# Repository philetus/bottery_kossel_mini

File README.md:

bottery kossel mini
===================

emerald bottery customizations for kossel mini reprap

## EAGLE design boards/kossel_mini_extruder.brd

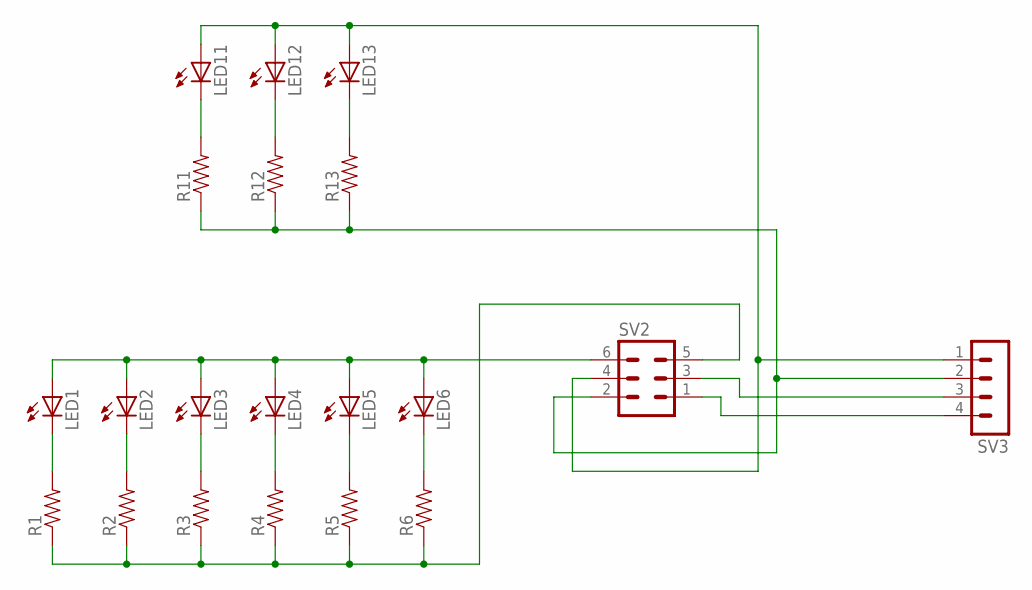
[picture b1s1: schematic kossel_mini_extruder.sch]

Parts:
LED1, LED2, LED3, LED4, LED5, LED6, LED11, LED12, LED13: LED0805; CHIPLED_0805
R1, R2, R3, R4, R5, R6, R11, R12, R13: RESISTOR0805-RES; 0805
SV2: MA03-2
SV3: MA04-1

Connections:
GND: R1.1, R2.1, R3.1, R4.1, R5.1, R6.1, SV2.5
HOT_12V: R11.1, R12.1, R13.1, SV2.2, SV3.2
HOT_SIG: LED11.A, LED12.A, LED13.A, SV2.4, SV3.1
unnamed: LED1.C, R1.2
unnamed: LED2.C, R2.2
unnamed: LED3.C, R3.2
unnamed: LED4.C, R4.2
unnamed: LED5.C, R5.2
unnamed: LED6.C, R6.2
unnamed: LED11.C, R11.2
unnamed: LED12.C, R12.2
unnamed: LED13.C, R13.2
THERM_GND: SV2.1, SV3.4
THERM_SIG: SV2.3, SV3.3
VCC: LED1.A, LED2.A, LED3.A, LED4.A, LED5.A, LED6.A, SV2.6

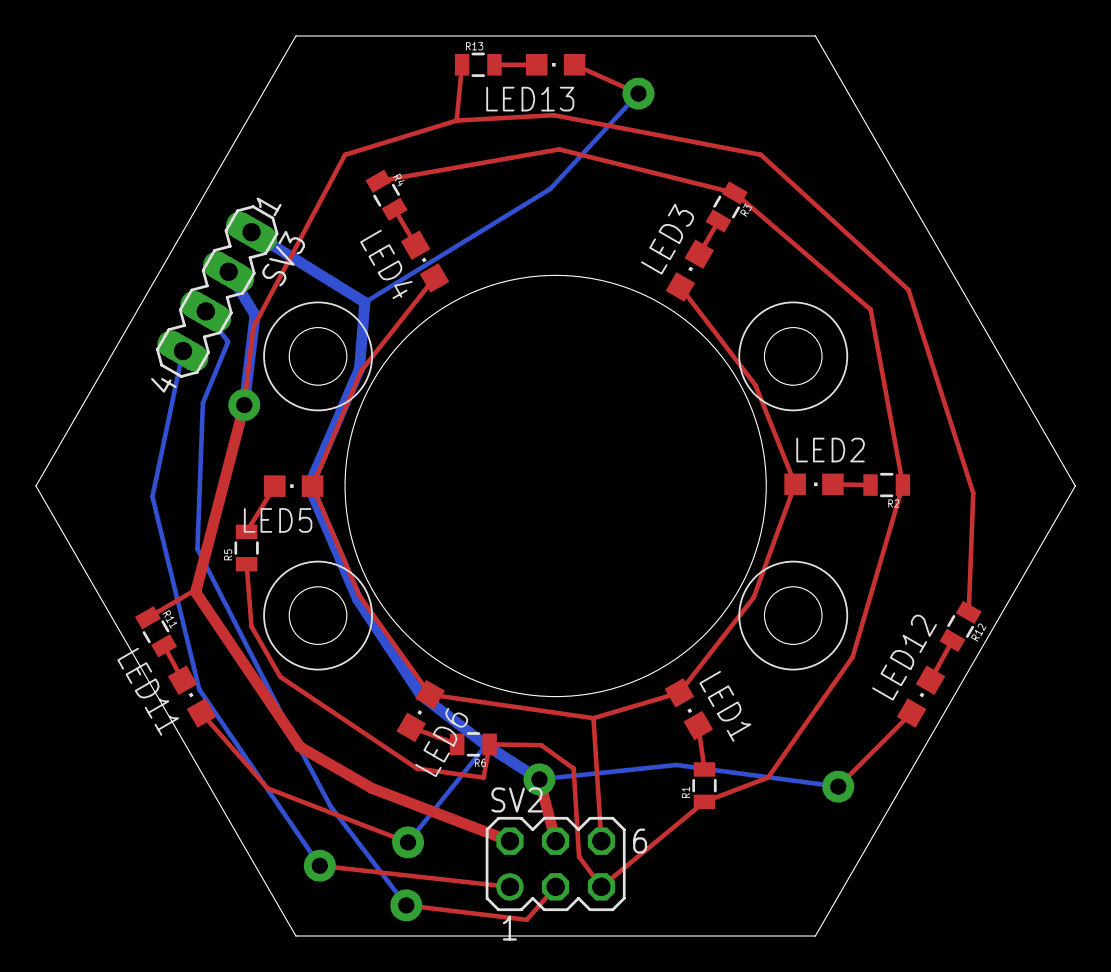
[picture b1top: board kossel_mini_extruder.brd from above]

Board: 4 copper layers, 57.7 x 50.0 mm, 20 parts (0 on the bottom side), 15 nets.

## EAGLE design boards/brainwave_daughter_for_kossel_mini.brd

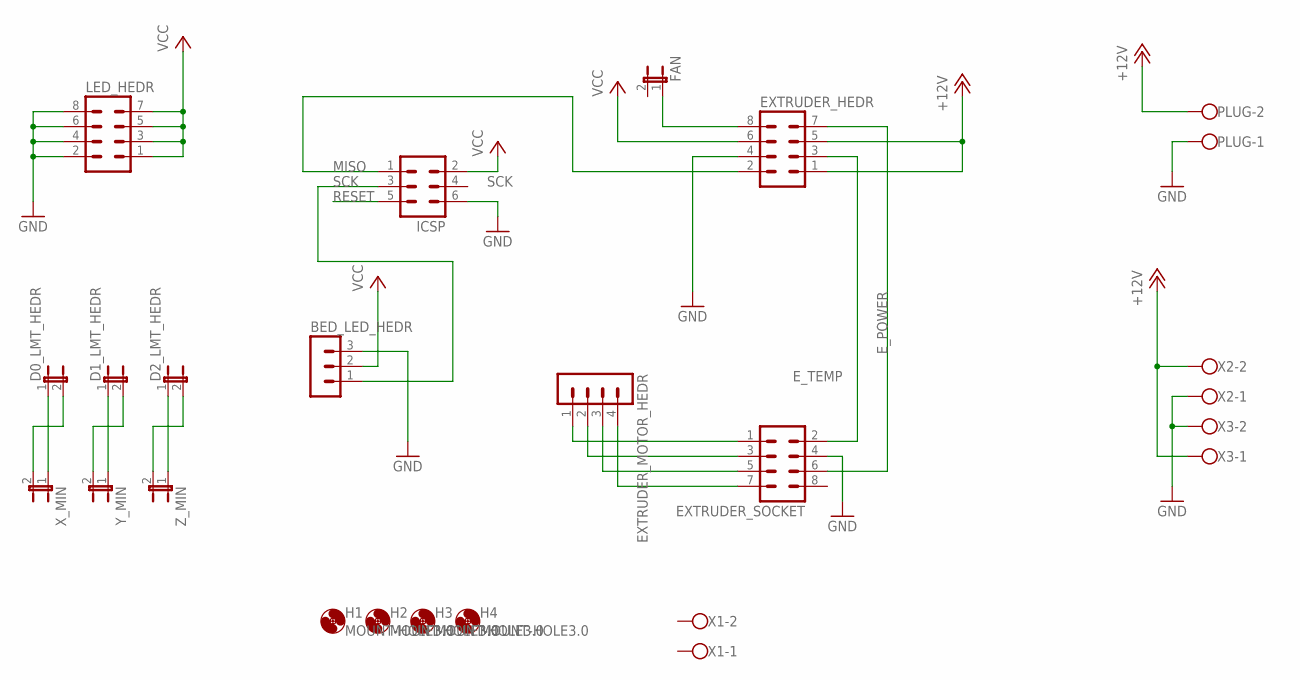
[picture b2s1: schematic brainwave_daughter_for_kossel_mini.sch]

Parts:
BED_LED_HEDR: MA03-1
D0_LMT_HEDR, D1_LMT_HEDR, D2_LMT_HEDR: JP1E; JP1
EXTRUDER_HEDR: MA04-2
EXTRUDER_MOTOR_HEDR: MA04-1
EXTRUDER_SOCKET: MA04-2
FAN: JP1E; JP1
H1, H2, H3, H4: MOUNT-HOLE3.0; 3,0
ICSP: MA03-2
LED_HEDR: MA04-2
PLUG: W237-102
X1, X3: W237-102; MPN 237-102
X2: W237-102
X_MIN: JP1E; JP1
Y_MIN: JP1E; JP1
Z_MIN: JP1E; JP1

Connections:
+12V: EXTRUDER_HEDR.1, EXTRUDER_HEDR.5, PLUG.2, X2.2, X3.1
E_POWER: EXTRUDER_HEDR.7, EXTRUDER_SOCKET.6
E_TEMP: EXTRUDER_HEDR.3, EXTRUDER_SOCKET.2
GND: BED_LED_HEDR.3, EXTRUDER_HEDR.4, EXTRUDER_SOCKET.4, ICSP.6, LED_HEDR.2, LED_HEDR.4, LED_HEDR.6, LED_HEDR.8, PLUG.1, X2.1, X3.2
MISO: EXTRUDER_HEDR.2, ICSP.1
unnamed: D0_LMT_HEDR.1, X_MIN.1
unnamed: D1_LMT_HEDR.1, Y_MIN.1
unnamed: D2_LMT_HEDR.1, Z_MIN.1
unnamed: D2_LMT_HEDR.2, Z_MIN.2
unnamed: D1_LMT_HEDR.2, Y_MIN.2
unnamed: D0_LMT_HEDR.2, X_MIN.2
unnamed: EXTRUDER_HEDR.8, FAN.1
unnamed: EXTRUDER_MOTOR_HEDR.1, EXTRUDER_SOCKET.1
unnamed: EXTRUDER_MOTOR_HEDR.2, EXTRUDER_SOCKET.3
unnamed: EXTRUDER_MOTOR_HEDR.3, EXTRUDER_SOCKET.5
unnamed: EXTRUDER_MOTOR_HEDR.4, EXTRUDER_SOCKET.7
RESET: ICSP.5
SCK: BED_LED_HEDR.1, ICSP.3
VCC: BED_LED_HEDR.2, EXTRUDER_HEDR.6, ICSP.2, LED_HEDR.1, LED_HEDR.3, LED_HEDR.5, LED_HEDR.7

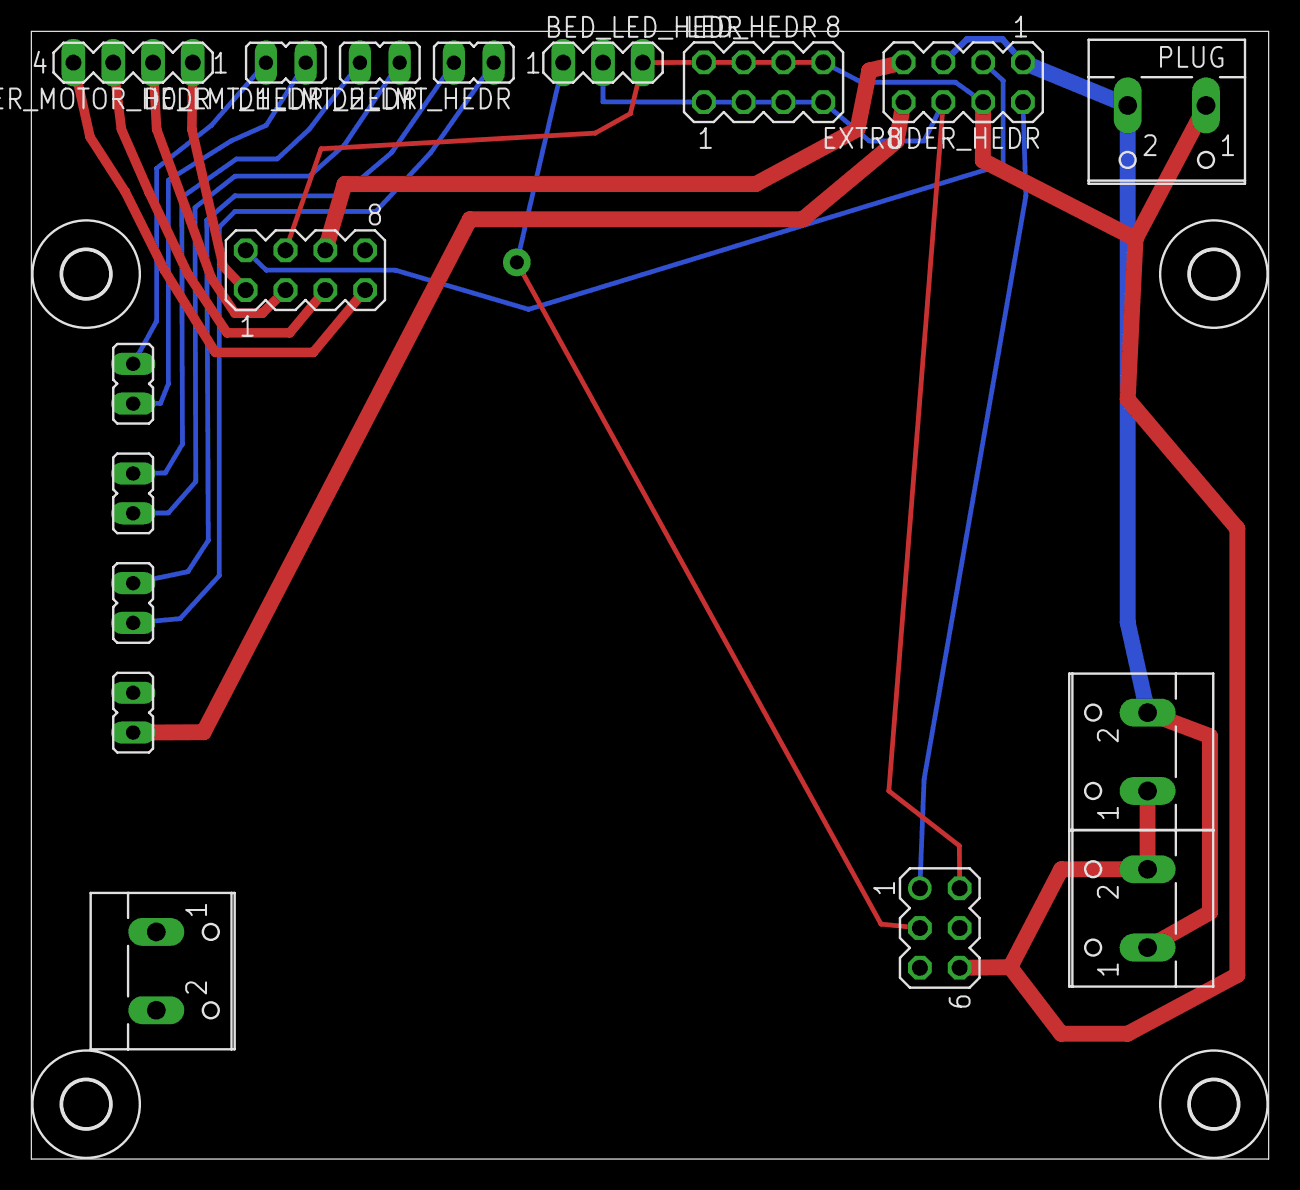
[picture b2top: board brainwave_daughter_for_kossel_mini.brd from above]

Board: 2 copper layers, 79.0 x 72.0 mm, 21 parts (0 on the bottom side), 18 nets.

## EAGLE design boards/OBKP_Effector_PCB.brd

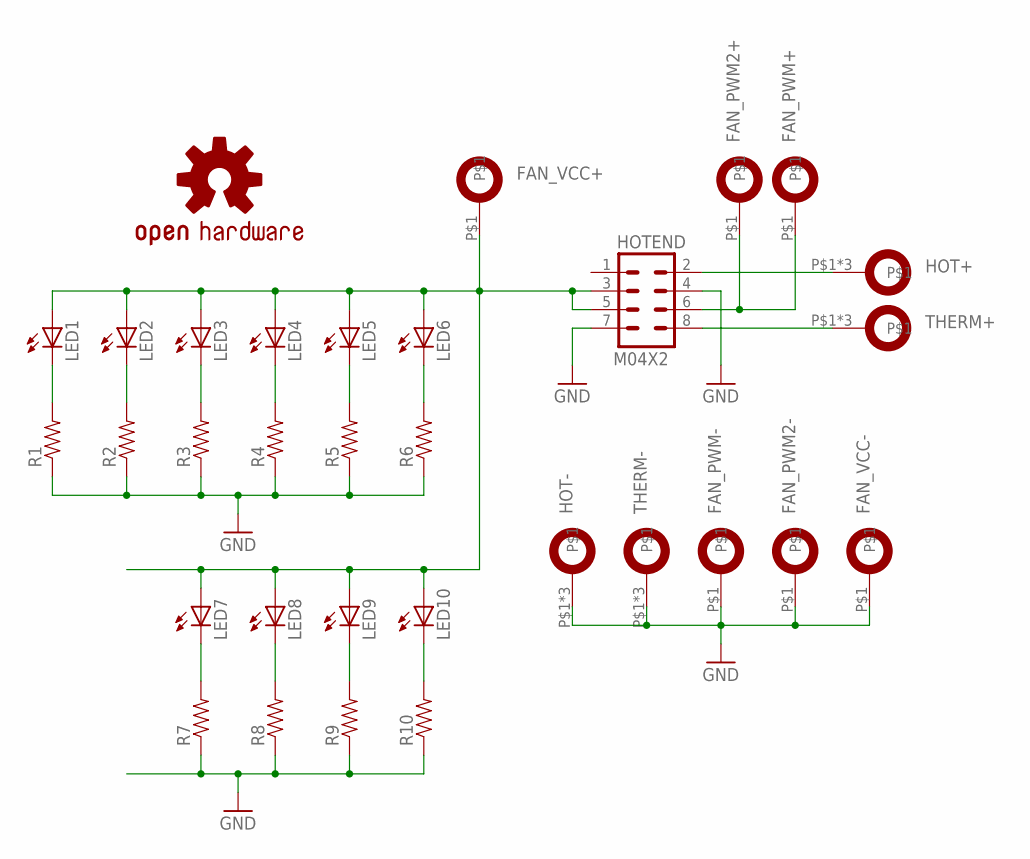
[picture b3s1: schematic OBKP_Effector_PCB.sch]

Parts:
FAN_PWM2+, FAN_PWM2-: LUG2.3; 2.3MM
FAN_PWM+: LUG2.3; 2.3MM
FAN_PWM-: LUG2.3; 2.3MM
FAN_VCC+: LUG2.3; 2.3MM
FAN_VCC-: LUG2.3; 2.3MM
HOT+: LUG3-X; 3MM
HOT-: LUG3-X; 3MM
HOTEND: M04X2; 2X4
LED1, LED2, LED3, LED4, LED5, LED6, LED7, LED8, LED9, LED10: LED0805; CHIPLED_0805
LOGO1: OSHW-LOGOS; OSHW-LOGO-S
R1, R2, R3, R4, R5, R6, R7, R8, R9, R10: RESISTOR0805-RES; 0805
THERM+: LUG3-X; 3MM
THERM-: LUG3-X; 3MM

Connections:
FAN_VCC: FAN_VCC+.P$1, HOTEND.3, HOTEND.5, LED1.A, LED2.A, LED3.A, LED4.A, LED5.A, LED6.A, LED7.A, LED8.A, LED9.A, LED10.A
GND: FAN_PWM2-.P$1, FAN_PWM-.P$1, FAN_VCC-.P$1, HOT-.P$1, HOT-.P$2, HOT-.P$3, HOTEND.4, HOTEND.7, R1.1, R2.1, R3.1, R4.1, R5.1, R6.1, R7.1, R8.1, R9.1, R10.1, THERM-.P$1, THERM-.P$2, THERM-.P$3
unnamed: LED1.C, R1.2
unnamed: LED2.C, R2.2
unnamed: LED3.C, R3.2
unnamed: LED4.C, R4.2
unnamed: LED5.C, R5.2
unnamed: LED6.C, R6.2
unnamed: LED7.C, R7.2
unnamed: LED8.C, R8.2
unnamed: HOT+.P$1, HOT+.P$2, HOT+.P$3, HOTEND.2
unnamed: HOTEND.8, THERM+.P$1, THERM+.P$2, THERM+.P$3
unnamed: FAN_PWM2+.P$1, FAN_PWM+.P$1, HOTEND.6
unnamed: LED9.C, R9.2
unnamed: LED10.C, R10.2

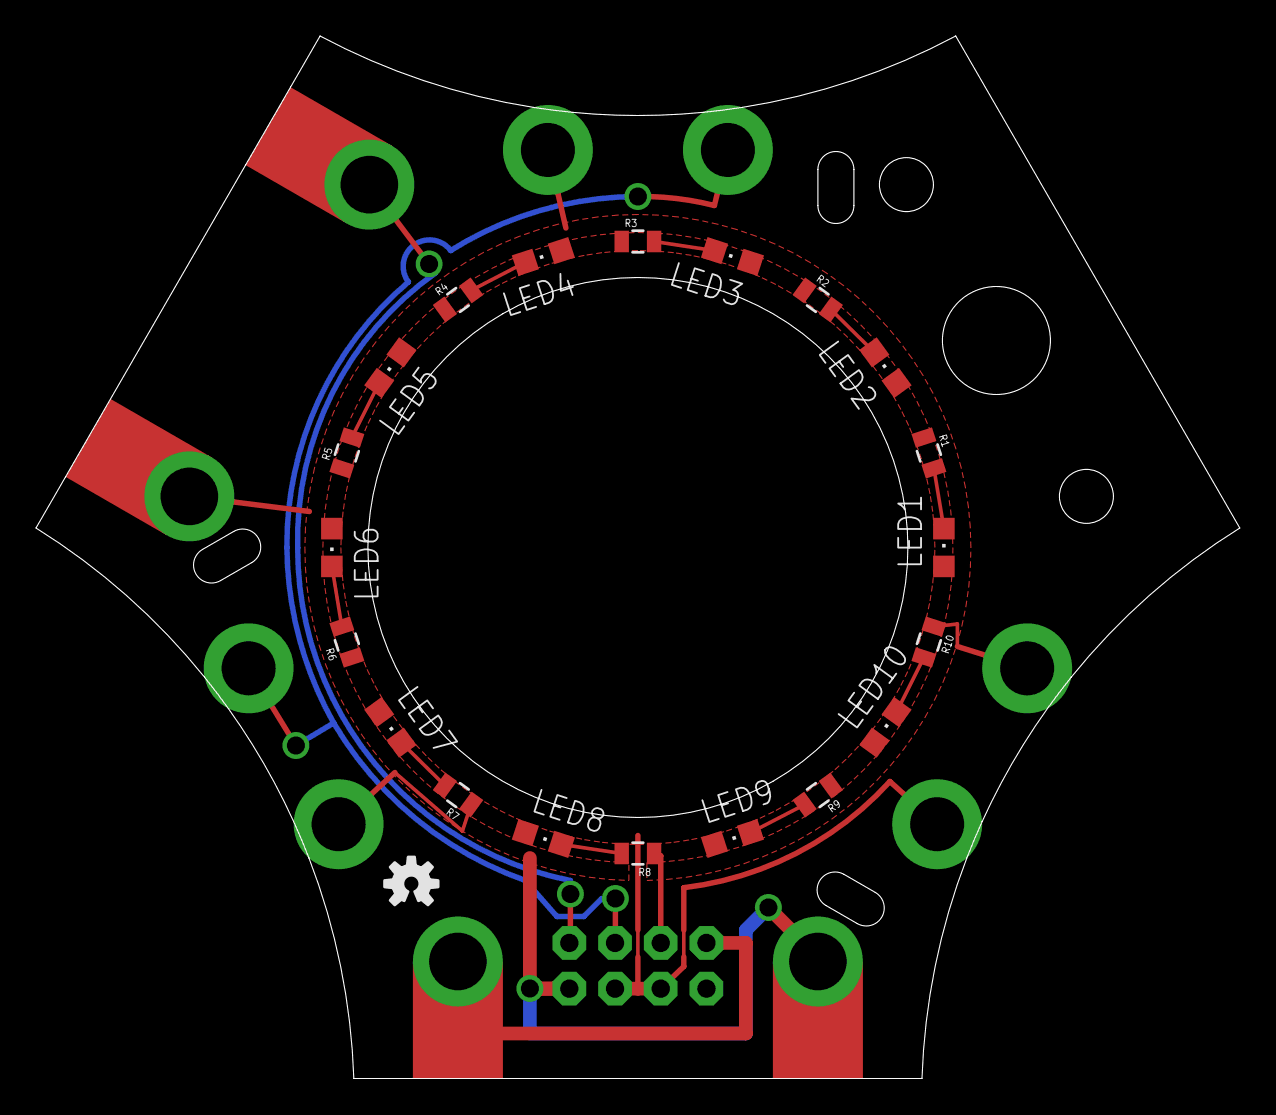
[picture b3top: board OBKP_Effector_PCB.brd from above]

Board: 4 copper layers, 66.9 x 57.9 mm, 32 parts (1 on the bottom side), 15 nets.

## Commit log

2013-12-07 modified extruder board design
2013-12-07 put fan vcc (12v!) on separate pin from led vcc (5v)
2013-12-07 created readme
2013-12-07 put third fan pwm pin on same net as other two
2013-12-07 imported kossel mini stl files and started rgb base clip model
2013-12-08 moved fan+ to hot+ net and fan- to fan pwm net and rerouted with burlier traces
2013-12-09 cleaned up board
2013-12-09 renamed extruder board
2013-12-09 added terence and wilsons original extruder board
2013-12-09 started brainwave daughter board for kossel mini
2013-12-09 finished first draft of extruder and daughter boards
2013-12-09 made vias beefier for hand soldering
2013-12-09 replaced 2x5 header with 2x4 header
2013-12-12 designed acrylic mounting panel for brainwave
2013-12-16 put fan on separate 12V supply line
2013-12-16 drawing for fan
2014-01-03 put fan and hot back on same 12v to make space to breakout thermister gnd
2014-01-07 removed fan stuff and added red leds
2014-01-07 oops
2014-01-11 moved red leds onto hot end circuit
2014-01-28 got models for push-to-connect and flange nut for new end effector from mcmaster
2014-01-28 got some stl models for kossel mini parts
2014-01-29 modeled end effector in solidworks 2012 from existing stl file
2014-01-29 reworked end effector to use captive flange nut to attach push to connect tube fitting
2014-01-29 scrounged some more of the right stls for kossel mini parts
2014-01-29 added cable stay panel designs for butterfly and cute bunny
2014-02-01 added laser cut designs for hot and cold end mounts
2014-02-04 added fan mount panel
2014-02-11 added plate clip
2014-02-26 modeled new autoprobe mount with space for teflon tube insert and track that returns probe without safety pin
2014-02-28 modeled limit switch for autoprobe
2014-03-01 redesigned end effector without autoprobe and with jhead held in mounting block
2014-03-02 refined jhead mounting block design
2014-03-02 added missing power supply clamp stl
2014-03-03 tweaked jhead mounting block design
2014-03-03 beefed up carriage
2014-03-03 made nut hole deeper
2014-03-05 started rev of end effector board
2014-03-05 grinding on effector board
2014-03-05 added outline of end effector platform to circuit board drawing
2014-03-05 still grinding on board
2014-03-06 turned stl right side up
2014-03-08 modeled simplified lower vertex
2014-03-08 first version of new extruder board
    and golden dog fan mount
2014-03-08 moved kossel extruder board to subfolder
2014-03-08 added gerber files
2014-03-09 created cable stay panel for golden dog
2014-03-10 lambo!
2014-03-24 modeled kossel mini frame assembly
2014-03-27 modeled plate pads and clips for force sensing resistors
2014-05-08 modeled geeetech jhead
2014-05-13 redesigned end effector group with geeetech (e3d) all metal jhead and 40mm cooling fan
2014-05-14 made stl files and pdf for new end effector group design
2014-05-14 made carriage channels wider
2014-05-24 reworked plate pad to work in both configurations to obviate mirrored version, made it less deep
2014-05-29 modified clip to work with 3 clips
2014-05-30 cleaned up new plate clip design
2014-05-30 redesigned fan mount block to raise circuit board
2014-05-30 further fan mount block redesign to improve airflow per johanns suggestion
2014-05-30 added cable strain relief holes to fan mount block, modeled end effector board
2014-05-31 tweaked end effector and fan mount block, generated pdf for end effector board

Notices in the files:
parts and their libraries:
SparkFun-LED: Licensing: CC v3.0 Share-Alike You are welcome to use this library for commercial purposes.
